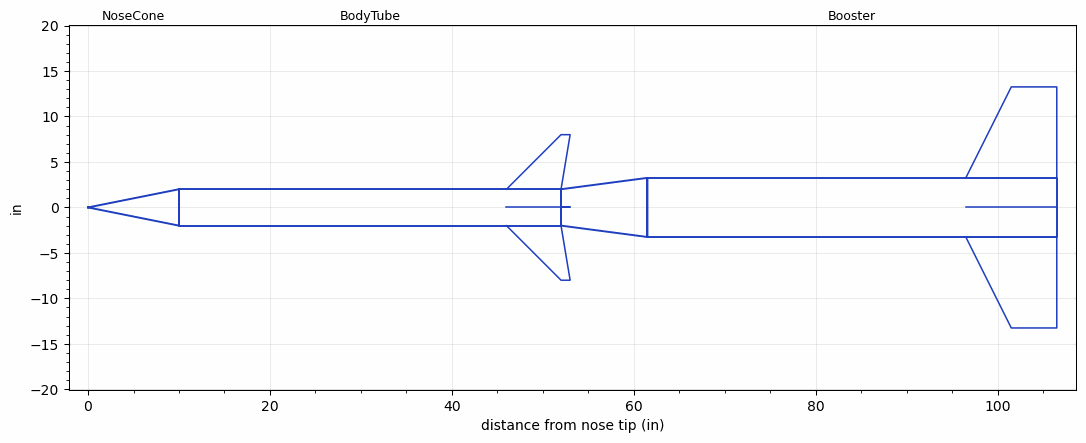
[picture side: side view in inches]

<RASAeroDocument>
 <FileVersion>2</FileVersion>
 <RocketDesign>
  <NoseCone>
   <Length>10</Length>
   <Diameter>4</Diameter>
   <Shape>Conical</Shape>
   <Location>0</Location>
  </NoseCone>
  <BodyTube>
   <Length>42</Length>
   <Diameter>4</Diameter>
   <Location>10</Location>
   <Fin>
    <Count>4</Count>
    <Chord>6</Chord>
    <Span>6</Span>
    <SweepDistance>6</SweepDistance>
    <TipChord>1</TipChord>
    <Thickness>0.1</Thickness>
    <LERadius>0.1</LERadius>
    <Location>6</Location>
    <AirfoilSection>Double Wedge</AirfoilSection>
    <FX1>0.1</FX1>
   </Fin>
  </BodyTube>
  <Booster>
   <Length>45</Length>
   <Diameter>6.5</Diameter>
   <InsideDiameter>4</InsideDiameter>
   <Location>52</Location>
   <ShoulderLength>9.5</ShoulderLength>
   <Fin>
    <Count>4</Count>
    <Chord>10</Chord>
    <Span>10</Span>
    <SweepDistance>5</SweepDistance>
    <TipChord>5</TipChord>
    <Thickness>0.1</Thickness>
    <LERadius>0.1</LERadius>
    <Location>10</Location>
    <AirfoilSection>Double Wedge</AirfoilSection>
    <FX1>0.1</FX1>
    <FX3>0.1</FX3>
   </Fin>
  </Booster>
  <Surface>Smooth (Zero Roughness)</Surface>
  <ModifiedBarrowman>False</ModifiedBarrowman>
  <Turbulence>False</Turbulence>
  <UseBooster1>False</UseBooster1>
  <UseBooster2>False</UseBooster2>
 </RocketDesign>
 <LaunchSite>
  <Altitude>0</Altitude>
  <Pressure>0</Pressure>
  <RodAngle>0</RodAngle>
  <RodLength>4</RodLength>
  <Temperature>74</Temperature>
  <WindSpeed>0</WindSpeed>
 </LaunchSite>
 <Recovery>
  <Altitude1>1000</Altitude1>
  <Altitude2>1000</Altitude2>
  <DeviceType1>None</DeviceType1>
  <DeviceType2>None</DeviceType2>
  <Event1>False</Event1>
  <Event2>False</Event2>
  <Size1>1</Size1>
  <Size2>1</Size2>
  <EventType1>None</EventType1>
  <EventType2>None</EventType2>
  <CD1>1.33</CD1>
  <CD2>1.33</CD2>
 </Recovery>
 <SimulationList>
  <Simulation>
   <SustainerEngine>O4200  (O4200)</SustainerEngine>
   <SustainerLaunchWt>60</SustainerLaunchWt>
   <SustainerNozzleDiameter>4</SustainerNozzleDiameter>
   <SustainerCG>25</SustainerCG>
   <SustainerIgnitionDelay>15</SustainerIgnitionDelay>
   <Booster1Engine>P9095  (MIT)</Booster1Engine>
   <Booster1LaunchWt>170</Booster1LaunchWt>
   <Booster1SeparationDelay>0</Booster1SeparationDelay>
   <Booster1IgnitionDelay>0</Booster1IgnitionDelay>
   <Booster1CG>70</Booster1CG>
   <Booster1NozzleDiameter>6</Booster1NozzleDiameter>
   <IncludeBooster1>True</IncludeBooster1>
   <Booster2Delay>0</Booster2Delay>
   <IncludeBooster2>False</IncludeBooster2>
   <TimetoApogee>173.7584</TimetoApogee>
   <MaxAltitude>391222.3</MaxAltitude>
   <MaxVelocity>4944.765</MaxVelocity>
  </Simulation>
 </SimulationList>
</RASAeroDocument>
